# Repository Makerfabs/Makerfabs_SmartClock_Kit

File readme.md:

# Makerfabs SmartClock Kit

```c++
/*
Version:        V1.2
Author:            Vincent
Create Date:    2021/4/14
Note:
    2023/5/12 V1.2:Change Weather API.
    2021/5/27 V1.1:Add product link and picture.

*/
```

[TOC]

# Makerfabs

[Makerfabs home page](https://www.makerfabs.com/)

[Makerfabs Wiki](https://wiki.makerfabs.com/)

# Makerfabs SmartClock Kit

​    It is a kit for starters. After 1~2 hours soldering and assembly, and easy steps to set the WiFi ssid and password by a phone, you will get: 

1. An real-time clock, it will get the world real-time from the Network timing protocol, you can set your local time zone easily 
2. An Alarm clock, with loud noise 
3. An Online world weather forecaster, about the local temperature/weather, you can easily change/alter your address/cities without any re-programming

## Intruduce

Product Link ：[DIY ESP32 SmartClock Kit with Weather Forecasting](https://www.makerfabs.com/diy-esp32-smartclock-kit.html) 

Wiki Link :  [No wiki]() 

Instruction Book : [DIY ESP32 Smart Clock Guide](https://www.makerfabs.com/desfile/files/DIY-ESP32-SmartClock-Guide-V1-5.pdf) 

## Feature

- ESP32 WROOM module: WiFi, Bluetooth, 4MB Flash
- 1.44inch 128*128 color display, ST7735 driver*
- Micro USB interface
- Support Arduino
- 450mAh battery, support charge
- Plug-in components, easy soldering

### Part List

- ESP32 SmartClock Kit Mainboard
- Batch of Capacitors& Resistors/Connectors
- Colorful LCD Module
- Lipo Battery
- Acrylic Boards
- Nuts & screws

# Firmware

## Equipment list

- SmartClock Kit
- Soldering iron

## Compiler Options

**If you have any questions，such as how to install the development board, how to download the code, how to install the library. Please refer to :[Makerfabs_FAQ](https://github.com/Makerfabs/Makerfabs_FAQ)**

- Install board : ESP32 .

- Install library : Adafruit_GFX library.

- Install library : Adafruit_ST7735 library.

- Install library : ArduinoJson library.

- Upload codes, select "ESP32 Dev Module" and "Huge APP"

## How To Use

[How to Make a DIY ESP32 SmartClock with Weather Forecasting](https://www.youtube.com/watch?v=e5g6aSs4Ocg&t=6s)

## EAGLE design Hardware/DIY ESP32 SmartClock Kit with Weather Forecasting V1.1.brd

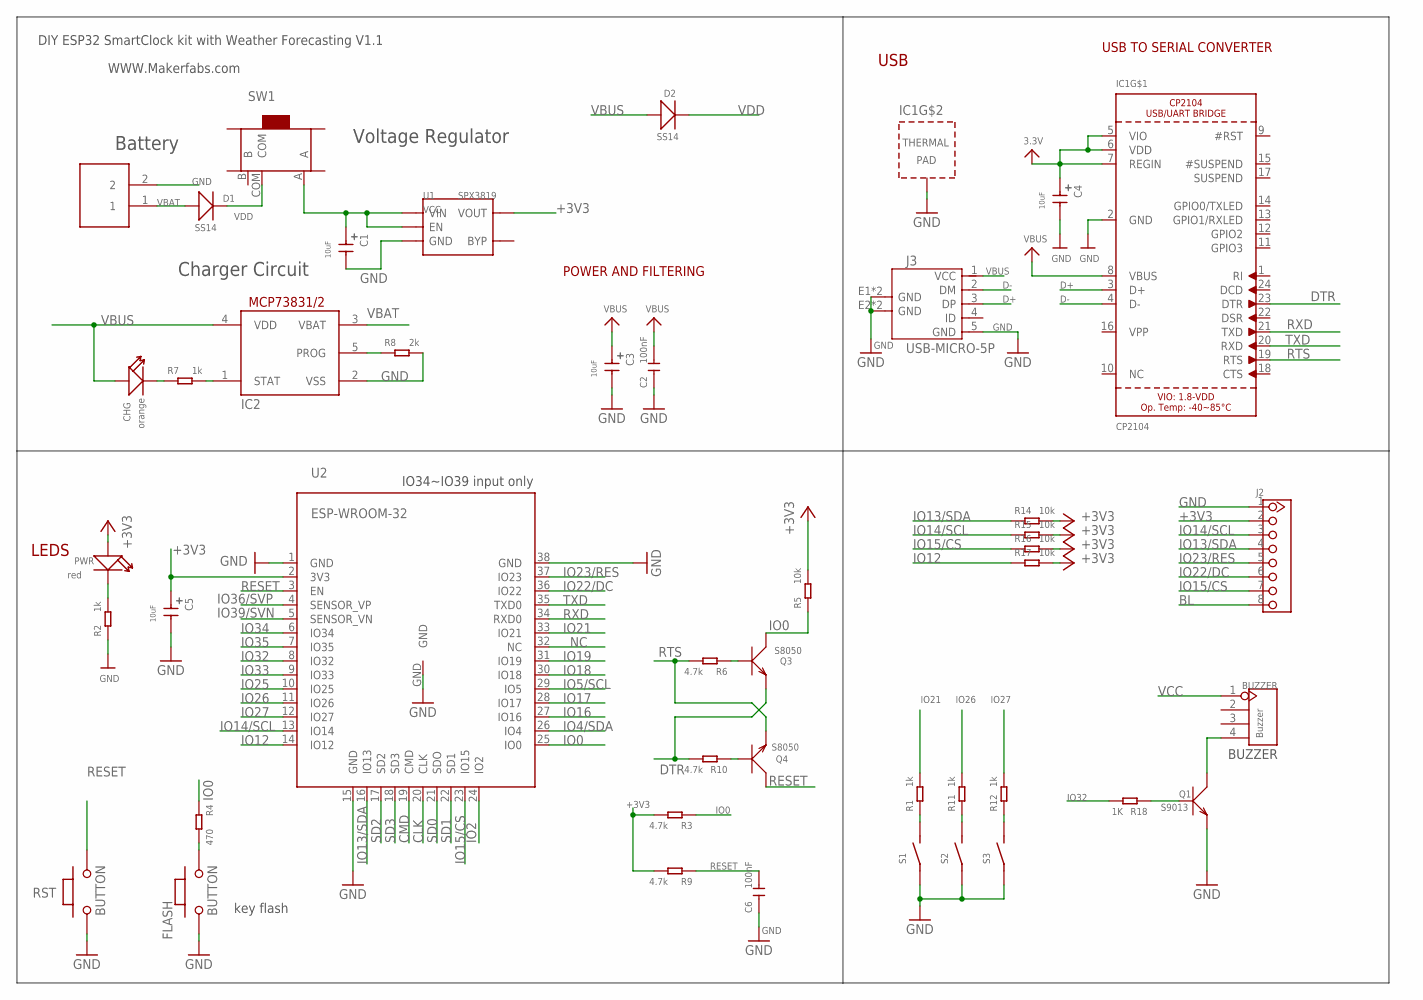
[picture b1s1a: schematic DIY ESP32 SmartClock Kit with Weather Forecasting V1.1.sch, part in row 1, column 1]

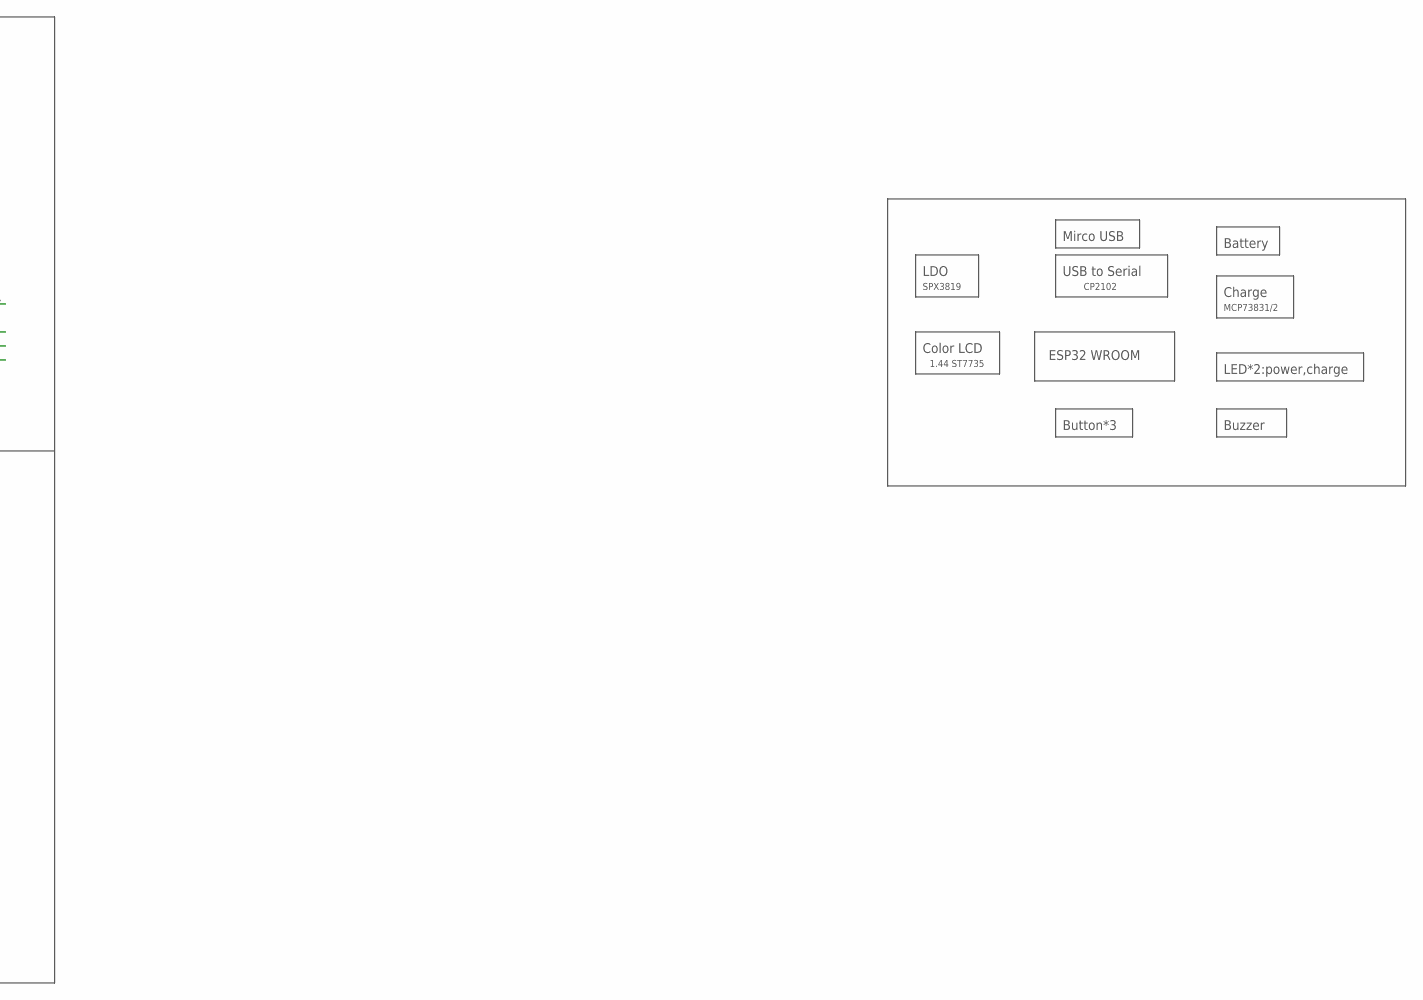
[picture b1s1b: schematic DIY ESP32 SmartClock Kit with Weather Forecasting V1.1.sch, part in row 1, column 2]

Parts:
BUZZER: Buzzer; 4P-65/35ROUND
C1, C3, C4, C5: 10uF; CAP_5*7
C2, C6: 100nF; CERAMIC-5.08
CHG: orange; LED-0603
D1, D2: SS14; SOD323
FLASH: BUTTON; 157SW
IC1: CP2104; QFN24_4MM_SMSC
IC2: MCP73831/OT; SOT23-5L
J1: PH2.0-2P-90-DIP
J2: HEADER-8P-2.54; 8P-2.54
J3: USB-MICRO-5P; MICRO-USB-5P
PWR: red; LED-0603
Q1: S9013; SOT23
Q3, Q4: S8050; SOT23
R1, R2, R7, R11, R12: 1k; 0204/7
R3, R6, R9, R10: 4.7k; 0204/7
R4: 470; 0204/7
R5, R14, R15, R16, R17: 10k; 0204/7
R8: 2k; 0204/7
R18: 1K; 0204/7
RST: BUTTON; 157SW
S1, S2, S3: BUTTON_4.54.5; 3*3_BUTTOM_DIP
SW1: SWITCH-3P-SMD-6.6X2.8; 3P-SMD-2CH-6.6X2.8-REINFORCE
U1: SPX3819; SOT23-5
U2: ESP-WROOM-32

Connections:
+3V3: C4.P$1 (1), C5.P$1 (1), IC1.5 (VIO), IC1.6 (VDD), IC1.7 (REGIN), J2.2, PWR.+, R3.2, R5.2, R9.2, R14.2, R15.2, R16.2, R17.2, U1.5 (VOUT), U2.2 (3V3)
BL: J2.8
CLK: U2.20 (CLK)
CMD: U2.19 (CMD)
D+: IC1.3 (D+), J3.3 (DP)
D-: IC1.4 (D-), J3.2 (DM)
DTR: IC1.23 (DTR), Q3.2 (E), R10.2
GND: C1.P$2 (2), C2.1, C3.P$2 (2), C4.P$2 (2), C5.P$2 (2), C6.1, FLASH.1, IC1.2 (GND), IC1.THERM (TP), IC2.2 (VSS), J1.2, J2.1, J3.5 (GND), J3.E1 (GND), J3.E2 (GND), J3.P1 (GND), J3.P2 (GND), Q1.2 (E), R2.1, R8.2, RST.1, S1.1, S1.2 (1), S2.1, S2.2 (1), S3.1, S3.2 (1), U1.2 (GND), U2.1 (GND), U2.15 (GND), U2.38 (GND), U2.GND
IO0: Q3.3 (C), R3.1, R4.1, R5.1, U2.25 (IO0)
IO2: U2.24 (IO2)
IO4/SDA: U2.26 (IO4)
IO5/SCL: U2.29 (IO5)
IO12: R17.1, U2.14 (IO12)
IO13/SDA: J2.4, R14.1, U2.16 (IO13)
IO14/SCL: J2.3, R15.1, U2.13 (IO14)
IO15/CS: J2.7, R16.1, U2.23 (IO15)
IO16: U2.27 (IO16)
IO17: U2.28 (IO17)
IO18: U2.30 (IO18)
IO19: U2.31 (IO19)
IO21: R1.2, U2.33 (IO21)
IO22/DC: J2.6, U2.36 (IO22)
IO23/RES: J2.5, U2.37 (IO23)
IO25: U2.10 (IO25)
IO26: R11.2, U2.11 (IO26)
IO27: R12.2, U2.12 (IO27)
IO32: R18.2, U2.8 (IO32)
IO33: U2.9 (IO33)
IO34: U2.6 (IO34)
IO35: U2.7 (IO35)
IO36/SVP: U2.4 (SENSOR_VP)
IO39/SVN: U2.5 (SENSOR_VN)
unnamed: R11.1, S2.3, S2.4 (3)
unnamed: BUZZER.4, Q1.3 (C)
unnamed: R12.1, S3.3, S3.4 (3)
unnamed: FLASH.2, R4.2
unnamed: PWR.-, R2.2
unnamed: Q4.1 (B), R10.1
unnamed: Q3.1 (B), R6.1
unnamed: R1.1, S1.3, S1.4 (3)
unnamed: Q1.1 (B), R18.1
unnamed: CHG.-, R7.1
unnamed: IC2.1 (STAT), R7.2
unnamed: IC2.5 (PROG), R8.1
NC: U2.32 (NC)
RESET: C6.2, Q4.3 (C), R9.1, RST.2, U2.3 (EN)
RTS: IC1.19 (RTS), Q4.2 (E), R6.2
RXD: IC1.21 (TXD), U2.34 (RXD0)
SD0: U2.21 (SDO)
SD1: U2.22 (SD1)
SD2: U2.17 (SD2)
SD3: U2.18 (SD3)
TXD: IC1.20 (RXD), U2.35 (TXD0)
VBAT: D1.+, IC2.3 (VBAT), J1.1
VBUS: C2.2, C3.P$1 (1), CHG.+, D2.+, IC1.8 (VBUS), IC2.4 (VDD), J3.1 (VCC)
VCC: BUZZER.1, C1.P$1 (1), SW1.A, U1.1 (VIN), U1.3 (EN)
VDD: D1.-, D2.-, SW1.COM

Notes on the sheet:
USB
LEDS
POWER AND FILTERING
USB TO SERIAL CONVERTER
IO34~IO39 input only
Battery
Voltage Regulator
Charger Circuit
BUZZER
ESP32 WROOM
Mirco USB
Charge
Buzzer
Button*3
LED*2:power,charge
Color LCD
1.44 ST7735
USB to Serial
CP2102
MCP73831/2
LDO
SPX3819
key flash
DIY ESP32 SmartClock kit with Weather Forecasting V1.1
WWW.Makerfabs.com

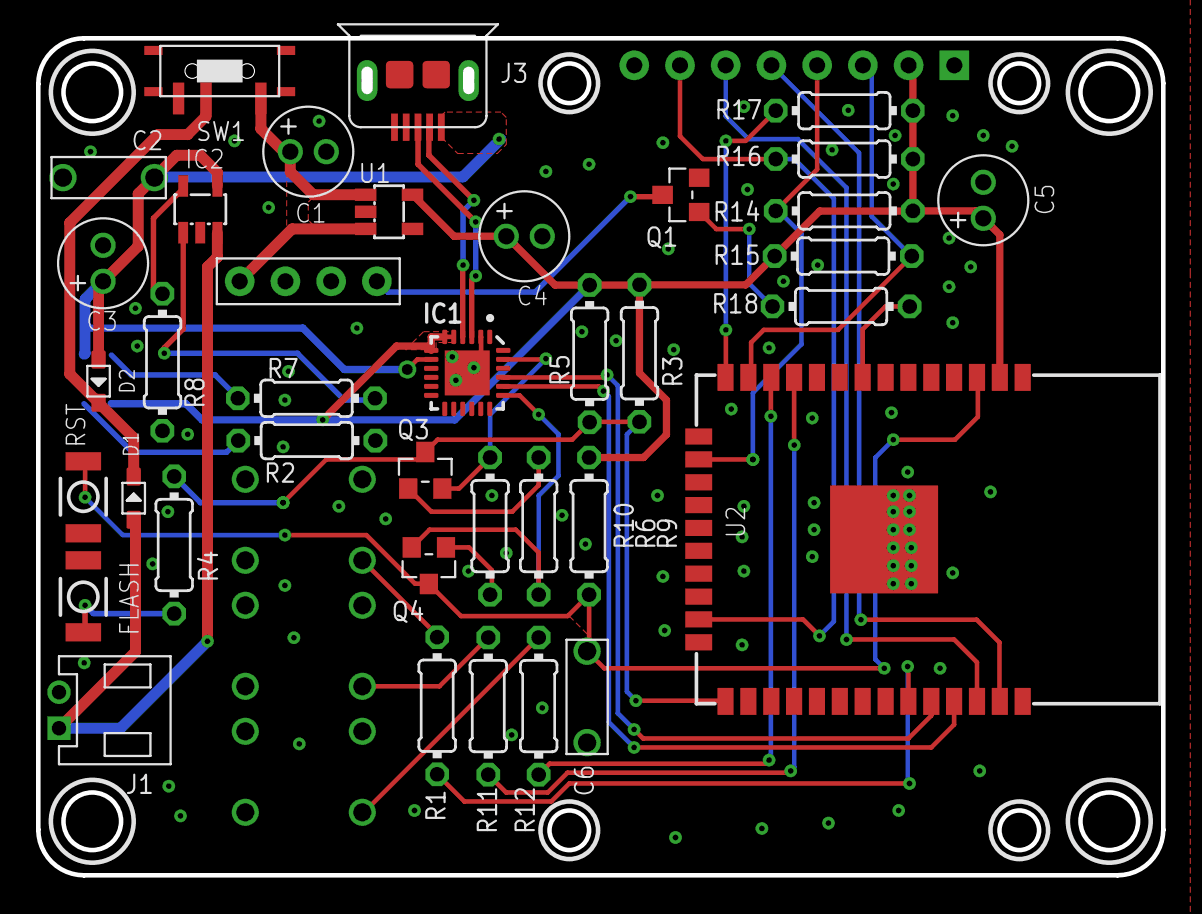
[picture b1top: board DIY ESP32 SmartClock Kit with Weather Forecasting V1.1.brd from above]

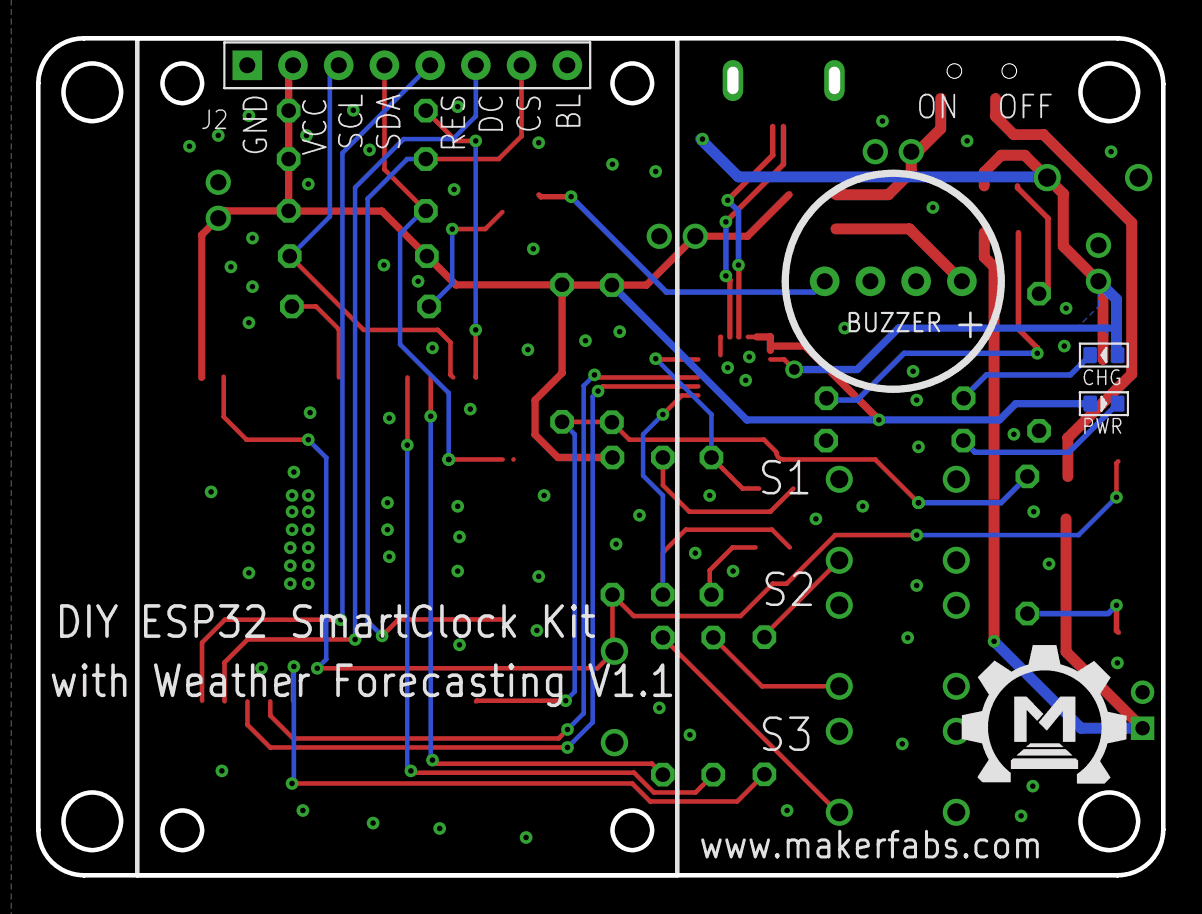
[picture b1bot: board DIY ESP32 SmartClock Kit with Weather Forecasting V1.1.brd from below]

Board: 2 copper layers, 62.1 x 46.1 mm, 45 parts (4 on the bottom side), 36 nets.

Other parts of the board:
U$1: MAKERFABS_0.3

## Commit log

2021-04-14 V1.0 Crerat Project
2021-04-16 Improve display
2021-04-28 Add log.
2021-05-08 create sch pcb
2021-05-10 Add timezone
2021-05-11 Fix bug,add timezone.
2021-05-27 V1.1 Add product link
2023-05-12 Change Weather API
2023-05-15 Add bin file

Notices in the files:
parts and their libraries:
microbuilder: This work is placed in the public domain, and may be freely used for commercial and non-commercial work with the following conditions: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
SparkFun-Aesthetics: Licensing: Creative Commons ShareAlike 4.0 International - https://creativecommons.org/licenses/by-sa/4.0
